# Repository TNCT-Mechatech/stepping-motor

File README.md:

# stepping-motor
ステッピングモータの基板です

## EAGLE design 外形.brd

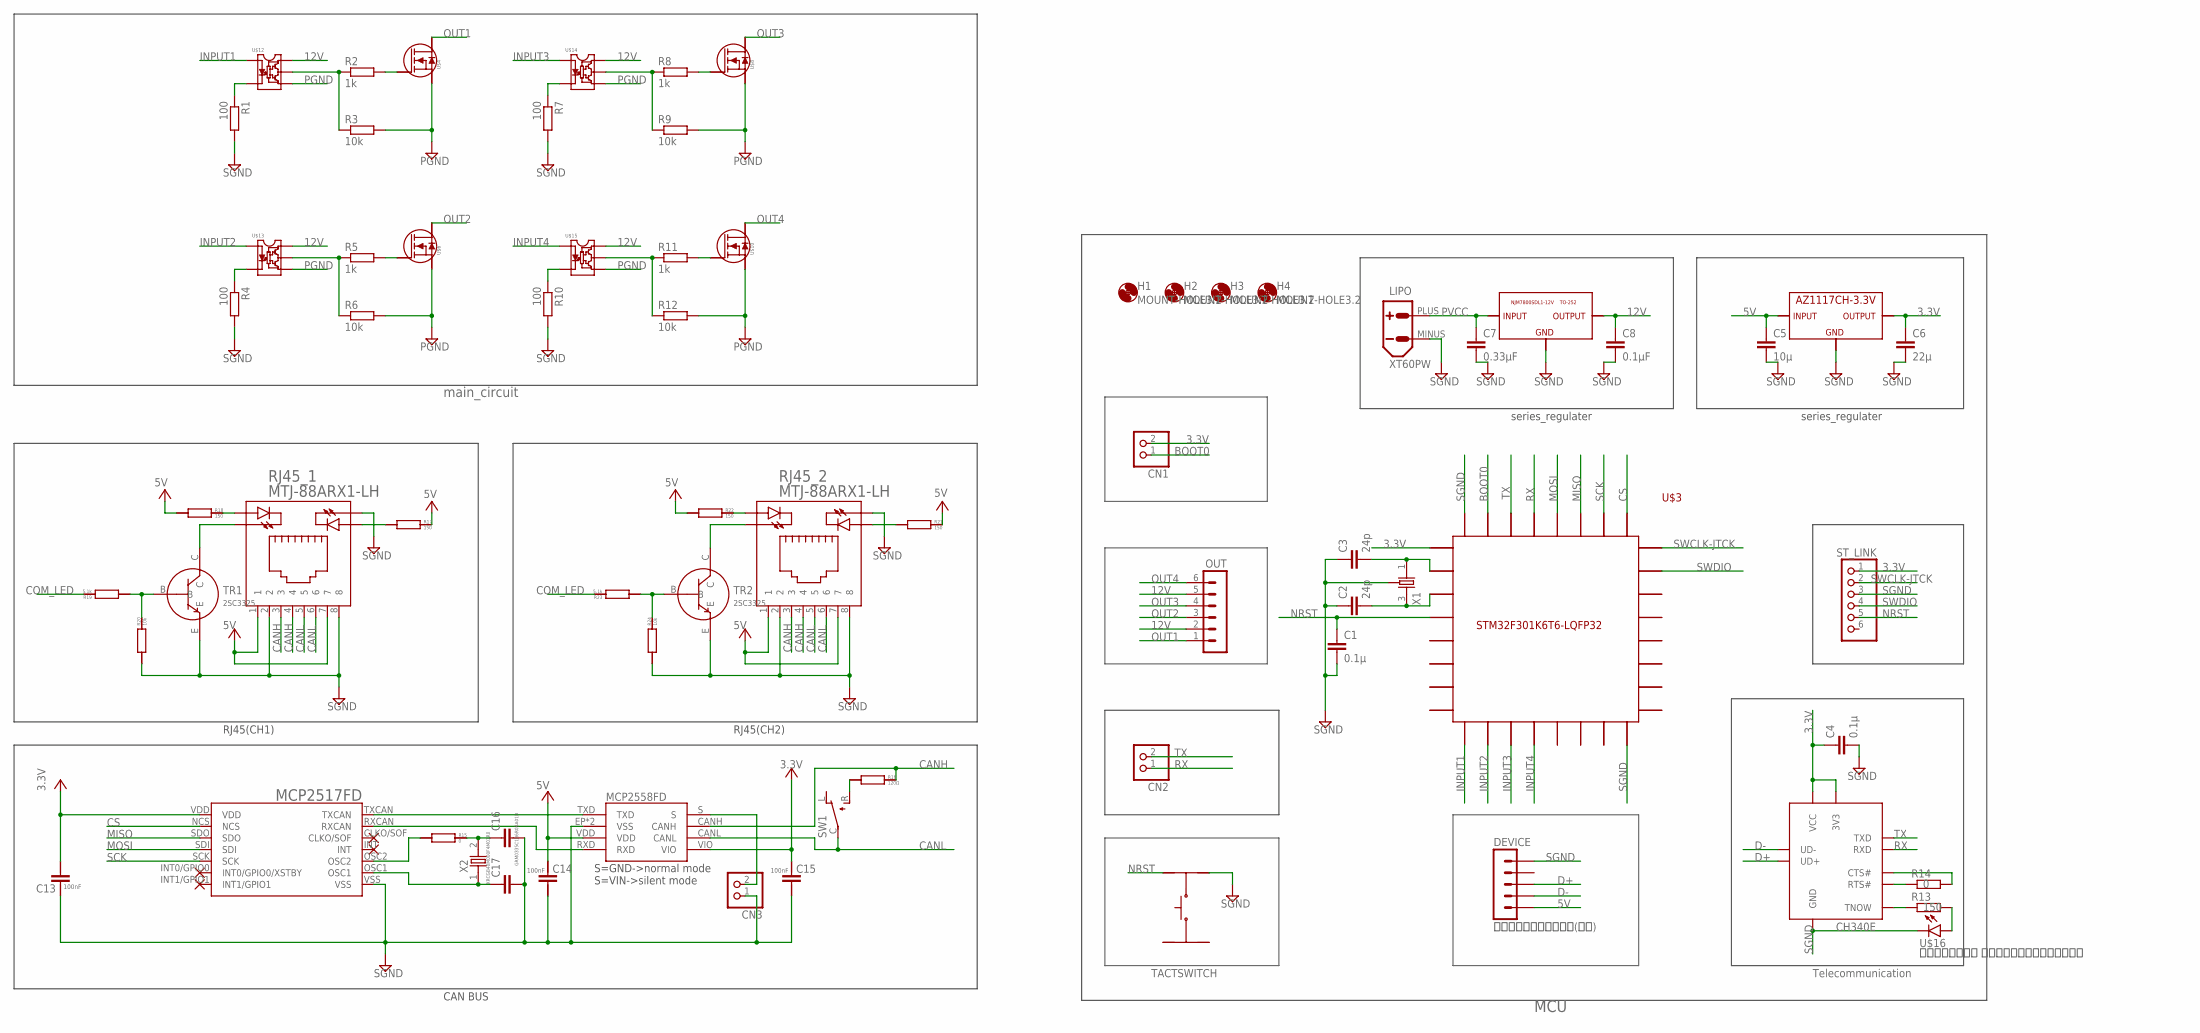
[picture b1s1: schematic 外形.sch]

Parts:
C1, C4: 0.1μ; GRM0335C1E240GA01D
C2, C3: 24p; GRM0335C1E240GA01D
C5: 10μ; GRM0335C1E240GA01D
C6: 22μ; GRM0335C1E240GA01D
C7: 0.33μF; GRM0335C1E240GA01D
C8: 0.1μF; GRM0335C1E240GA01D
C13, C14, C15: GCM188L81H104KA57
C16, C17: GRM0335C1H6R0BA01D; GRM0335C1H120GA01
CN1, CN2, CN3: PINHD-1X2; 1X02
DEVICE: ＵＳＢコネクタ・ミニＢ(メス)
H1, H2, H3, H4: MOUNT-HOLE3.2; 3,2
LIPO: XT60PW
OUT: 06-JST; B6B-XH
R1, R4, R7, R10: 100; M1206
R2, R5, R8, R11: 1k; M1206
R3, R6, R9, R12: 10k; M1206
R13: 150; M1206
R14: 0; M1206
R15: 0; CR0603
R16: 120Ω; CR0603
R17, R18, R21, R22: 150; CR0603
R19, R23: 5.1k; CR0603
R20, R24: 10k; CR0603
REGYURETA: ３．３V; ＡＺ１１１７ＣＨ－３．３ＴＲＧ１
RJ45_1, RJ45_2: MTJ-88ARX1-LH
ST_LINK: PINHD-1X6; 1X06
SW1: SS-12SDP2
TR1, TR2: 2SC3325
U1: CH340E; MSOP-10
U2: MCP2517FD
U$1: MCP2558FD
U$3: STM32K6T6-LQFP32; STM32F301K6T6-LQFP32
U$4, U$6, U$8, U$10: PXN012-60QL
U$5: TACTSWITCH
U$12, U$13, U$14, U$15: TLP155E
U$16: ３ｍｍ白色ＬＥＤ ＬＥＢＷＬ３４Ａ０６ＡＡ００; LED5MM
U$17: NJM7800SDL1-12V
X1: RH100-24.000-18-1020-EXT-TR
X2: XRCGB40M000F4M01R0; XRCGB40M000F4M00R0

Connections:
3.3V: C4.1, C6.1, C13.P$2, C15.P$1, CN1.2, REGYURETA.OUTPUT, REGYURETA.VOUT (OUTPUT), ST_LINK.1, U1.3V3, U1.VCC, U2.VDD, U$1.VIO, U$3.VDD1
5V: C5.1, C14.P$1, DEVICE.VBUS (1), R17.RIGHT, R18.LEFT, R21.RIGHT, R22.LEFT, REGYURETA.INPUT, RJ45_1.1, RJ45_1.7, RJ45_2.1, RJ45_2.7, U$1.VDD
12V: C8.1, OUT.2, OUT.5, U$12.VCC, U$13.VCC, U$14.VCC, U$15.VCC, U$17.VOUT (OUTPUT)
BOOT0: CN1.1, U$3.BOOT0
CANH: R16.RIGHT, RJ45_1.3, RJ45_1.4, RJ45_2.3, RJ45_2.4, U$1.CANH
CANL: RJ45_1.5, RJ45_1.6, RJ45_2.5, RJ45_2.6, SW1.C, U$1.CANL
COM_LED: R19.RIGHT, R23.RIGHT
CS: U2.NCS, U$3.PA15
D+: DEVICE.D+ (3), U1.UD+
D-: DEVICE.D- (2), U1.UD-
INPUT1: U$3.PA3, U$12.ANODE
INPUT2: U$3.PA4, U$13.ANODE
INPUT3: U$3.PA5, U$14.ANODE
INPUT4: U$3.PA6, U$15.ANODE
MISO: U2.SDO, U$3.PB4 (PB3)
MOSI: U2.SDI, U$3.PB5 (PB4)
unnamed: R2.2, U$4.GATE
unnamed: R5.2, U$6.GATE
unnamed: R13.2, U$16.A
unnamed: R13.1, U1.TNOW
unnamed: R1.1, U$12.CATHODE
unnamed: R4.1, U$13.CATHODE
unnamed: R14.1, U1.RTS#
unnamed: R14.2, U1.CTS#
unnamed: C2.2, U$3.PF1/OSC_OUT, X1.3 (2)
unnamed: R7.1, U$14.CATHODE
unnamed: R8.2, U$8.GATE
unnamed: R11.2, U$10.GATE
unnamed: R10.1, U$15.CATHODE
unnamed: C3.2, U$3.PF0/OSC_IN, X1.1
unnamed: R16.LEFT, SW1.R
unnamed: U2.TXCAN, U$1.TXD
unnamed: U2.RXCAN, U$1.RXD
unnamed: R15.LEFT, U2.OSC2
unnamed: C17.1, U2.OSC1, X2.1
unnamed: C16.1, R15.RIGHT, X2.2
unnamed: R17.LEFT, RJ45_1.LED2_A
unnamed: R21.LEFT, RJ45_2.LED2_A
unnamed: CN3.2, U$1.S
unnamed: R18.RIGHT, RJ45_1.LED1_A
unnamed: R22.RIGHT, RJ45_2.LED1_A
unnamed: RJ45_1.LED1_K, TR1.C
unnamed: RJ45_2.LED1_K, TR2.C
unnamed: R23.LEFT, R24.RIGHT, TR2.B
unnamed: R19.LEFT, R20.RIGHT, TR1.B
NRST: C1.1, ST_LINK.5, U$3.NRST, U$5.P$1
OUT1: OUT.1, U$4.DRAIN1 (DRAIN), U$4.DRAIN2 (DRAIN), U$4.DRAIN3 (DRAIN), U$4.DRAIN4 (DRAIN)
OUT2: OUT.3, U$6.DRAIN1 (DRAIN), U$6.DRAIN2 (DRAIN), U$6.DRAIN3 (DRAIN), U$6.DRAIN4 (DRAIN)
OUT3: OUT.4, U$8.DRAIN1 (DRAIN), U$8.DRAIN2 (DRAIN), U$8.DRAIN3 (DRAIN), U$8.DRAIN4 (DRAIN)
OUT4: OUT.6, U$10.DRAIN1 (DRAIN), U$10.DRAIN2 (DRAIN), U$10.DRAIN3 (DRAIN), U$10.DRAIN4 (DRAIN)
PGND: R3.2, R6.2, R9.2, R12.2, U$4.SOURCE1 (SOURCE), U$4.SOURCE2 (SOURCE), U$4.SOURCE3 (SOURCE), U$6.SOURCE1 (SOURCE), U$6.SOURCE2 (SOURCE), U$6.SOURCE3 (SOURCE), U$8.SOURCE1 (SOURCE), U$8.SOURCE2 (SOURCE), U$8.SOURCE3 (SOURCE), U$10.SOURCE1 (SOURCE), U$10.SOURCE2 (SOURCE), U$10.SOURCE3 (SOURCE), U$12.GND, U$13.GND, U$14.GND, U$15.GND
PVCC: C7.1, LIPO.PLUS (+), U$17.VIN (INPUT)
RX: CN2.1, U1.RXD, U$3.PB6 (PB5)
SCK: U2.SCK, U$3.PB3 (PB2)
SGND: C1.2, C2.1, C3.1, C4.2, C5.2, C6.2, C7.2, C8.2, C13.P$1, C14.P$2, C15.P$2, C16.2, C17.2, CN3.1, DEVICE.GND (5), LIPO.MINUS (-), R1.2, R4.2, R7.2, R10.2, R20.LEFT, R24.LEFT, REGYURETA.ADJ/GND (GND), RJ45_1.2, RJ45_1.8, RJ45_1.LED2_K, RJ45_2.2, RJ45_2.8, RJ45_2.LED2_K, ST_LINK.3, TR1.E, TR2.E, U1.GND, U2.VSS, U$1.EP (VSS), U$1.VSS, U$3.VSS1, U$3.VSS2, U$5.P$3, U$16.K (C), U$17.GND, X1.2 (SHIELD), X1.4 (SHIELD)
SWCLK-JTCK: ST_LINK.2, U$3.PA14
SWDIO: ST_LINK.4, U$3.PA13
TX: CN2.2, U1.TXD, U$3.PB7 (PB6)
V1: R2.1, R3.1, U$12.VOUT
V2: R5.1, R6.1, U$13.VOUT
V3: R8.1, R9.1, U$14.VOUT
V4: R11.1, R12.1, U$15.VOUT

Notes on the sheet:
TACTSWITCH
Telecommunication
S=GND->normal mode S=VIN->silent mode
RJ45(CH1)
RJ45(CH2)
CAN BUS
series_regulater
main_circuit
MCU

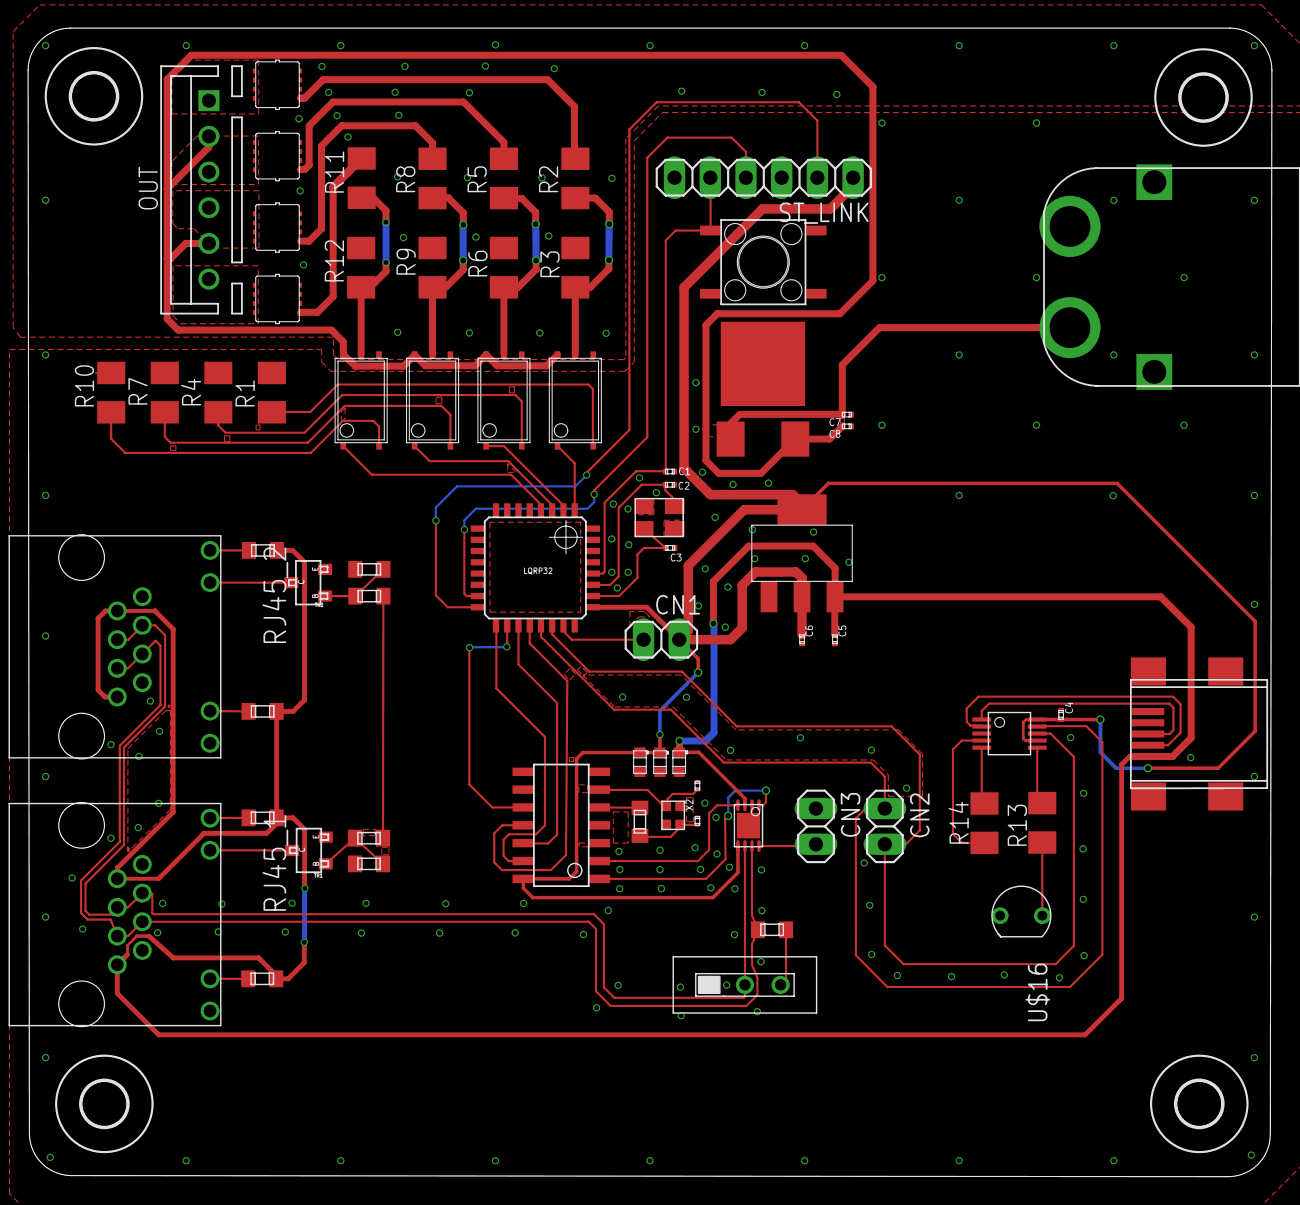
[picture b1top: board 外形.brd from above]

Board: 2 copper layers, 88.5 x 81.7 mm, 71 parts (0 on the bottom side), 62 nets.

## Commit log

2023-04-14 Update LICENSE
